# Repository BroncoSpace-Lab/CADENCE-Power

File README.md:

This repository contains the development of the Solar and Battery Management system Boards that will be used for the CADENCE mission.

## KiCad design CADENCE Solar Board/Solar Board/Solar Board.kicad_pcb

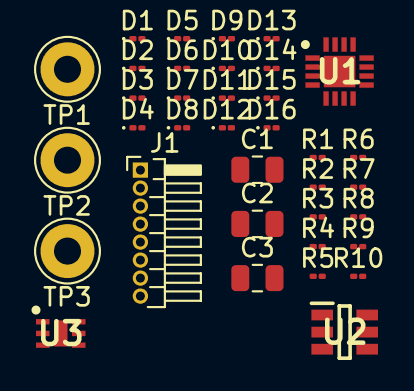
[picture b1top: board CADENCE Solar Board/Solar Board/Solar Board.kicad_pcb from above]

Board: 2 copper layers, 36 parts (0 on the bottom side), 32 nets, no tracks yet.

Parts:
C1, C3: 100nF; C_0805_2012Metric
C2: 10uF; C_0805_2012Metric
D1, D2, D3, D4, D5, D6, D7, D8, D9, D10, D11, D12, D13, D14, D15, D16: D; D_01005_0402Metric
J1: Conn_01x08; PinHeader_1x08_P1.00mm_Horizontal
R1, R2, R3, R5, R6, R7, R8, R10: 10k; R_01005_0402Metric
R4: 0.01; R_01005_0402Metric
R9: 1k; R_01005_0402Metric
TP1: Sensor Input; Pin_D1.3mm_L11.0mm_LooseFit
TP2: S1+; Pin_D1.3mm_L11.0mm_LooseFit
TP3: S1-; Pin_D1.3mm_L11.0mm_LooseFit
U1: INA230AIRGTT; QFN50P300X300X100-17N-D
U2: AD7414ARTZ-1REEL7; SOT95P280X145-6N
U3: OPT3001IDNPRQ1; SON65P200X200X65-7N-D

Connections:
+3.3V: C1.2, J1.1, R1.2, R4.1, R7.1, R8.2, R10.2, TP1.1 (1_1), U1.11 (BUS), U1.12 (IN-), U2.3 (VDD), U3.1 (VDD)
GND: C1.1, C2.2, C3.2, J1.4, U1.1 (A1), U1.2 (A0), U1.10 (GND), U2.2 (GND), U3.2 (ADDR), U3.3 (GND_1), U3.7 (GND_2)
HS_I2C1_LCL: J1.7, R3.2, R5.1, U3.4 (SCL)
HS_I2C1_LDA: J1.8, R2.1, R6.1, U3.6 (SDA)
unnamed: D1.2 (A), D2.2 (A)
unnamed: D1.1 (K), D4.2 (A)
unnamed: D2.1 (K), D3.2 (A)
unnamed: D3.1 (K), D6.2 (A)
unnamed: D4.1 (K), D8.2 (A)
unnamed: D5.2 (A), D6.1 (K)
unnamed: D7.2 (A), D8.1 (K)
unnamed: D5.1 (K), D10.2 (A)
unnamed: D9.2 (A), D10.1 (K)
unnamed: D11.2 (A), D12.1 (K)
unnamed: D11.1 (K), D16.2 (A)
unnamed: D7.1 (K), D12.2 (A)
unnamed: D13.2 (A), D14.1 (K)
unnamed: D13.1 (K), D15.1 (K)
unnamed: D9.1 (K), D14.2 (A)
unnamed: D15.2 (A), D16.1 (K)
unnamed: R1.1, U1.3 (ALERT)
unnamed: R4.2, U1.13 (IN+)
unnamed: R3.1, U1.5 (SCL)
unnamed: R2.2, U1.4 (SDA)
unnamed: R10.1, U1.9 (V_S+)
unnamed: C2.1, C3.1, R7.2, R9.2, U2.5 (ALERT)
unnamed: R9.1, U2.1 (AS)
unnamed: R5.2, U2.4 (SCL)
unnamed: R6.2, U2.6 (SDA)
unnamed: R8.1, U3.5 (INT)
Solar1+: J1.2, J1.3, TP2.1 (1_1)
Solar1-: J1.5, J1.6, TP3.1 (1_1)

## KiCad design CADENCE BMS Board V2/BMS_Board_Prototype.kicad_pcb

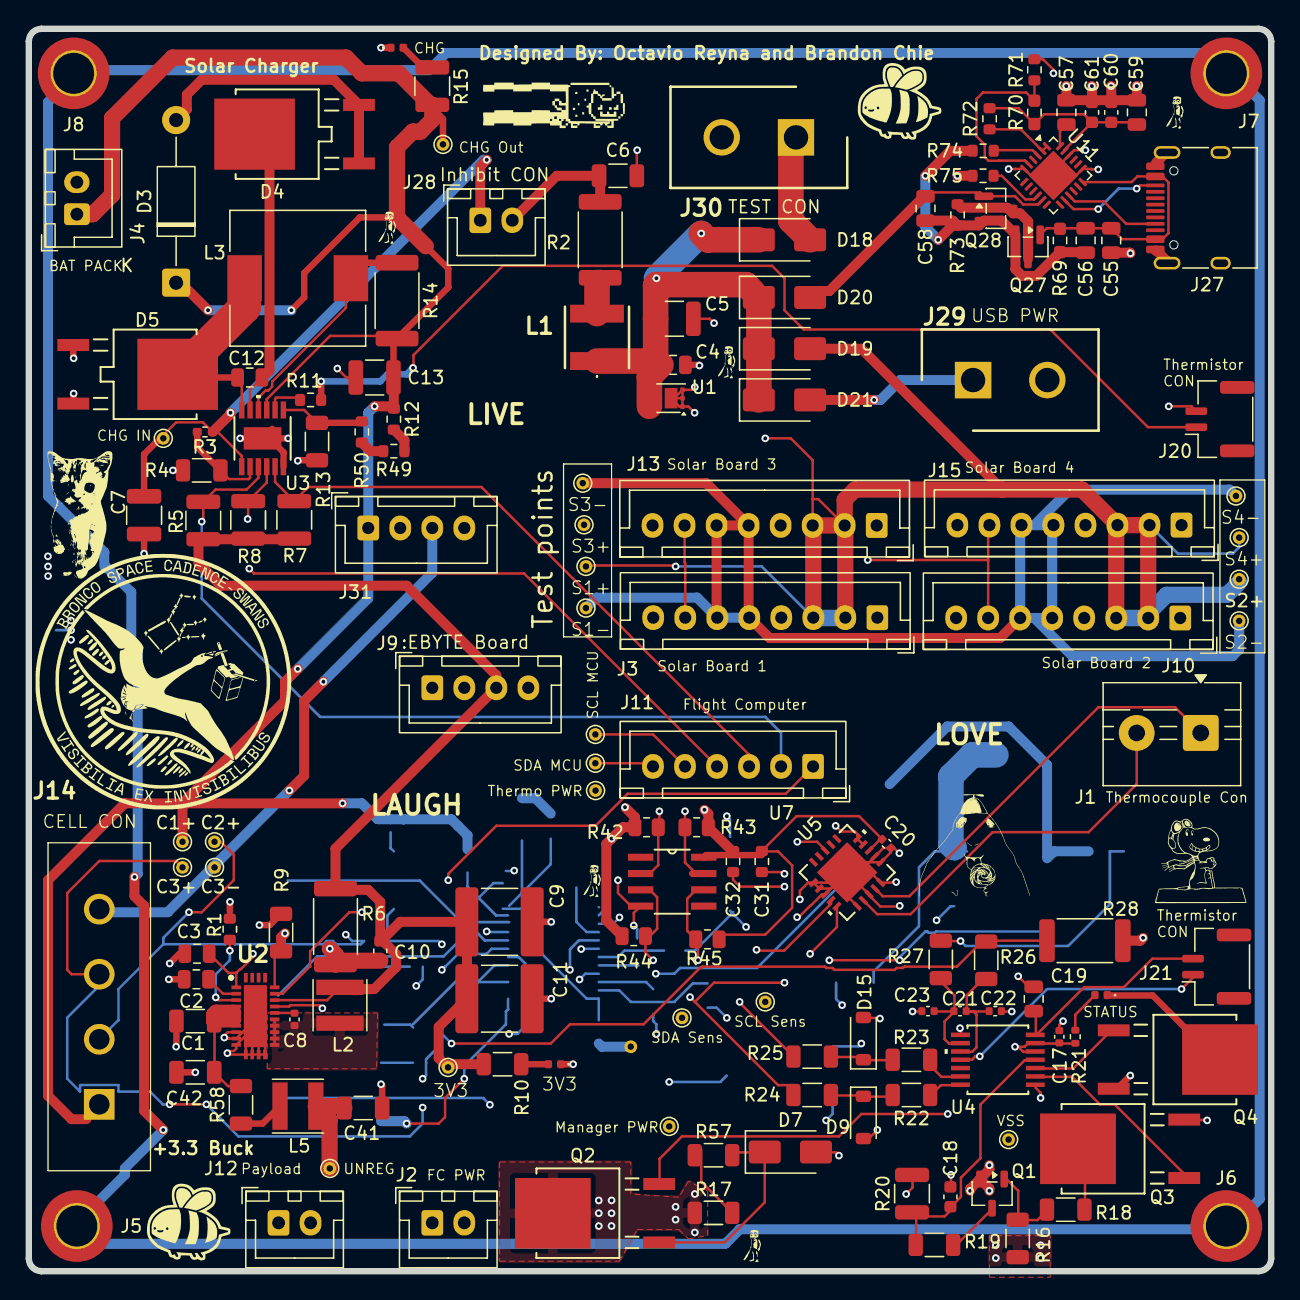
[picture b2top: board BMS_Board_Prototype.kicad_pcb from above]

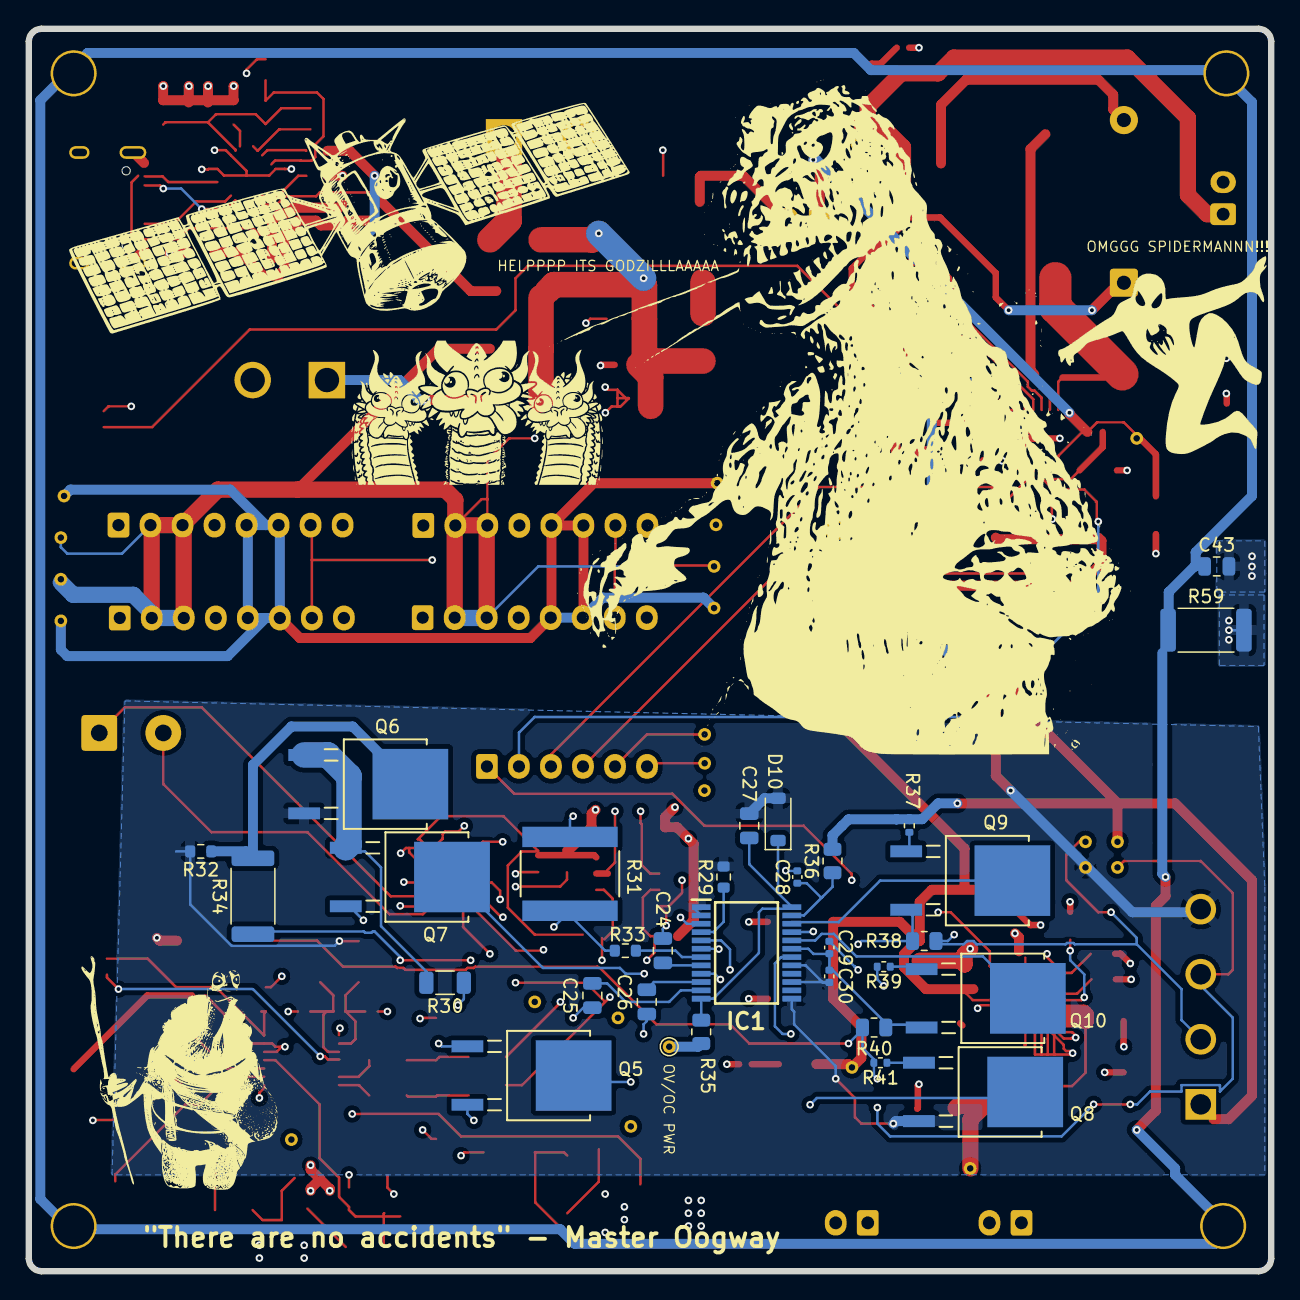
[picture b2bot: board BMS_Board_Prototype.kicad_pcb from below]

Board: 4 copper layers, 97.0 x 97.0 mm, 180 parts (31 on the bottom side), 98 nets.

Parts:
C1, C6, C41, C42: 4.7uF; C_1206_3216Metric
C1+: C1+; TestPoint_THTPad_D1.0mm_Drill0.5mm
C2, C4: 10nF; C_0805_2012Metric
C2+: C2+; TestPoint_THTPad_D1.0mm_Drill0.5mm
C3, C12, C19, C27, C56, C57, C58, C59: 1uF; C_0805_2012Metric
C3+: C3+; TestPoint_THTPad_D1.0mm_Drill0.5mm
C3-: C3-; TestPoint_THTPad_D1.0mm_Drill0.5mm
C5, C7, C13: 10uF; C_1210_3225Metric
C8, C17, C20, C21, C22, C23, C28, C29, C30: 100nF; C_0402_1005Metric
C9, C11: 47uF; C_2220_5750Metric
C10: 4.7pF; C_0603_1608Metric
C18: 3300pF; C_0603_1608Metric
C24, C55: 3.3uF; C_0805_2012Metric
C25: 2200pF; C_0805_2012Metric
C26: .47uF; C_0805_2012Metric
C31: 1uF; R_0603_1608Metric
C32: 100nF; R_0603_1608Metric
C43: 1nF; C_0805_2012Metric
C60, C61: 100nF; C_0603_1608Metric
D2: 3V3; LED_0402_1005Metric
D3: 1N4730APF-M (3V9); D_DO-41_SOD81_P12.70mm_Horizontal
D4, D5: STPS1045B-TR; DPAK_STM
D6: CHG; LED_0402_1005Metric
D7: 5V6; D_SMA
D8: LED; D_0402_1005Metric
D9, D15: 3.5V; D_SOD-123
D10: 15V; D_SOD-123
D18, D19, D20, D21: D_Schottky 40v; D_SMA
IC1: R5432V407BA; SOP65P760X140-24N
J1: Screw_Terminal_01x02; TerminalBlock_MaiXu_MX126-5.0-02P_1x02_P5.00mm
J2, J4, J12, J28: Conn_01x02; JST_XH_B2B-XH-A_1x02_P2.50mm_Vertical
J3, J10, J13, J15: Conn_01x08; JST_XH_B8B-XH-A_1x08_P2.50mm_Vertical
J5, J6, J7, J8: Conn_01x01_Socket; MountingHole_3.2mm_M3_DIN965_Pad_TopOnly
J9, J31: Conn_01x04; JST_XH_B4B-XH-A_1x04_P2.50mm_Vertical
J11: Conn_01x06; JST_XH_B6B-XH-A_1x06_P2.50mm_Vertical
J14: Conn_01x04; LC04T
J20, J21: Conn_01x02; JST_GH_SM02B-GHS-TB_1x02-1MP_P1.25mm_Horizontal
J27: USB_C_Receptacle_USB2.0_16P; USB_C_Receptacle_HRO_TYPE-C-31-M-12
J29, J30: Conn_01x02; SHDR2W120P580X500_2X1_790X1380X1460P
L1: 4.7u; FNR5040S4R7MT
L2: 1.8uH; L_Taiyo-Yuden_NR-40xx
L3: 22uH; L_10.4x10.4_H4.8
L5: 1uH; L_Taiyo-Yuden_NR-40xx
Q1: P-Channel FET; SOT-23-3
Q2, Q3, Q4: 60V Enhancement; SOT_N06-31-GE3_VIS
Q5, Q6, Q7: Q_NMOS_DSG; SOT_N06-31-GE3_VIS
Q8, Q9, Q10: N-MOS; SOT_N06-31-GE3_VIS
Q27, Q28: Q_PMOS_DGS; SOT-23
R1: 18.2k; R_0603_1608Metric
R2, R14: 0.1; R_2512_6332Metric
R3: 590k; R_0402_1005Metric_Pad0.72x0.64mm_HandSolder
R4, R16: 100k; R_1206_3216Metric
R5: 47k; R_1210_3225Metric
R6, R34, R59: 1M; R_2512_6332Metric
R7, R8: 10k; R_1210_3225Metric
R9: 412k; R_1206_3216Metric
R10: 4.7K; R_1206_3216Metric
R11: 910; R_0603_1608Metric
R12, R49: 470k; R_0603_1608Metric
R13: 340k; R_1206_3216Metric
R15: 10K; R_1210_3225Metric
R17, R57: 52.3k; R_1206_3216Metric
R18: 165k; R_1206_3216Metric
R19: 215K; R_1206_3216Metric
R20: 16.5k; R_1210_3225Metric
R21: 330; R_0402_1005Metric
R22, R23, R24, R25, R26, R27: 100; R_1206_3216Metric
R28: .037; R_2512_6332Metric
R29, R33, R75: 10K; R_0603_1608Metric
R30: 11.5K; R_1206_3216Metric
R31: .05; STA_CSSH2728_STP
R32: 2M; R_0603_1608Metric
R35, R36, R38, R40, R42, R43: 330; R_0805_2012Metric
R37, R39, R41: 100; R_0402_1005Metric
R44, R45: 4.7K; R_0805_2012Metric
R50: 1k; R_0603_1608Metric
R58: 0.1; R_1206_3216Metric
R69: 10K; R_0603_1608Metric_Pad0.98x0.95mm_HandSolder
R70: 5.1K; R_0603_1608Metric_Pad0.98x0.95mm_HandSolder
R71: 2.4K; R_0603_1608Metric
R72: 0; R_0603_1608Metric
R73, R74: 49.9K; R_0603_1608Metric
TP1: UNREG; TestPoint_THTPad_D1.0mm_Drill0.5mm
TP2: Charger-IN; TestPoint_THTPad_D1.0mm_Drill0.5mm
TP3: 3V3; TestPoint_THTPad_D1.0mm_Drill0.5mm
TP4: Charger-Out; TestPoint_THTPad_D1.0mm_Drill0.5mm
TP5: Manager-PWR; TestPoint_THTPad_D1.0mm_Drill0.5mm
TP6: VSS; TestPoint_THTPad_D1.0mm_Drill0.5mm
TP7: Thermo-PWR; TestPoint_THTPad_D1.0mm_Drill0.5mm
TP8: OV/OC PWR; TestPoint_THTPad_D1.0mm_Drill0.5mm
TP9: S1-; TestPoint_THTPad_D1.0mm_Drill0.5mm
TP10: S1+; TestPoint_THTPad_D1.0mm_Drill0.5mm
TP11: S2+; TestPoint_THTPad_D1.0mm_Drill0.5mm
TP12: S2-; TestPoint_THTPad_D1.0mm_Drill0.5mm
TP13: S3+; TestPoint_THTPad_D1.0mm_Drill0.5mm
TP14: S3-; TestPoint_THTPad_D1.0mm_Drill0.5mm
TP15: S4+; TestPoint_THTPad_D1.0mm_Drill0.5mm
TP16: S4-; TestPoint_THTPad_D1.0mm_Drill0.5mm
TP17: SDA-MCU; TestPoint_THTPad_D1.0mm_Drill0.5mm
TP18: SCL-MCU; TestPoint_THTPad_D1.0mm_Drill0.5mm
TP19: SDA-Sensor; TestPoint_THTPad_D1.0mm_Drill0.5mm
TP20: SCL-Sensor; TestPoint_THTPad_D1.0mm_Drill0.5mm
U1: TVS2200DRV; WSON-6-1EP_2x2mm_P0.65mm_EP1x1.6mm
U2: LT8612; QFN50P300X600X80-29N-D
U3: LT3652IMSE#PBF; MSOP-12_MSE_LIT
U4: BQ34Z100-R2; PW14_TEX
U5: MCP9600-E_MX; MQFN20_NU_MCH
U7: P82B715DR; D8
U11: CYPD3177-24LQ; QFN-24-1EP_4x4mm_P0.5mm_EP2.75x2.75mm

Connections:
3V3 Power Good: J11.1, U2.23 (PG)
+3.3V: C9.2, C10.2, C11.2, C20.2, C31.1, C32.1, J3.1, J9.3, J10.1, J13.1, J15.1, L2.2, R5.1, R6.2, R7.1, R8.1, R10.1, R42.1, R43.1, R44.1, R45.1, R75.1, TP3.1 (1_1), TP7.1 (1_1), U2.22 (BIAS), U5.8 (VDD), U7.8 (Vcc)
/Power/3v3 Feedback: C10.1, R6.1, R9.1, U2.24 (FB)
/Power/3v3 SW: C8.1, L2.1, U2.15 (SW), U2.16 (SW), U2.17 (SW), U2.18 (SW), U2.19 (SW)
/Sensors/REGIN: C17.1, Q2.2 (S), R21.1, U4.5 (CE), U4.6 (REGIN)
/Sensors/Serial Clock: R23.1, U4.13 (P4/SCL)
/Sensors/Serial Data: R22.1, U4.14 (P3/SDA)
/Sensors/Voltage Divider: C18.2, R19.2, R20.1, U4.4 (BAT)
/Sensors/Voltage Divider Enable: Q3.3 (D), R18.2
CB1: IC1.22 (CB1), Q9.3 (G)
CB2: IC1.20 (CB2), Q10.3 (G)
CB3: IC1.18 (CB3), Q8.3 (G)
CC1: J27.A5 (CC1), U11.15 (CC1)
CC2: J27.B5 (CC2), U11.14 (CC2)
CHG': J11.4, R8.2, U3.4 (~CHRG)
Cell 1+: C1+.1 (1_1), C13.1, D3.1 (K), J4.1, J14.1, J31.1, R12.1, R14.2, R15.1, R36.2, R37.2, TP4.1 (1_1), U3.9 (BAT)
Cell 2+: C2+.1 (1_1), J14.2, R38.2, R39.2
Cell 3+: C3+.1 (1_1), J14.3, R26.2, R28.1, R40.2, R41.2
Cell 3-: C3-.1 (1_1), C27.2, C30.2, D10.2 (A), IC1.1 (CTLC), IC1.2 (CTLD), IC1.13 (SEL2), IC1.15 (VC5), IC1.17 (VC4), J14.4, J31.3, Q6.2 (S), Q8.2 (S), R27.2, R28.2, R29.2, R32.2
DRAIN: IC1.5 (DRAIN), Q5.3 (G)
FAULT': J11.3, R7.2, U3.5 (~FAULT)
HS_I2C1_LCL: J3.7, J10.7, J11.5, J13.7, J15.7, R43.2, TP18.1 (1_1), U7.7 (Ly)
HS_I2C1_LDA: J3.8, J10.8, J11.6, J13.8, J15.8, R42.2, TP17.1 (1_1), U7.2 (Lx)
HS_I2C1_SCL: R25.2, R45.2, TP20.1 (1_1), U5.19 (SCL), U7.6 (Sy)
HS_I2C1_SDA: R24.2, R44.2, TP19.1 (1_1), U5.20 (SDA), U7.3 (Sx)
NTC: J20.1, R11.2
unnamed: C43.1, J5.1 (1_1), J6.1 (1_1), J7.1 (1_1), J8.1 (1_1), R59.1
unnamed: D2.2 (A), R10.2
unnamed: D3.2 (A), D4.1 (A)
unnamed: C12.2, D4.2 (K), U3.11 (BOOST)
unnamed: C12.1, D5.2 (K), L3.1, U3.12 (SW)
unnamed: D6.2 (A), R15.2
unnamed: D7.1 (K), Q2.1 (G), R57.2
unnamed: D8.2 (A), R21.2
unnamed: D8.1 (K), Q4.3 (D)
unnamed: D9.1 (K), R22.2, R24.1
unnamed: D15.1 (K), R23.2, R25.1
unnamed: C4.1, C5.1, D18.1 (K), D19.1 (K), D20.1 (K), D21.1 (K), L1.1, U1.4 (IN), U1.5 (IN), U1.6 (IN)
unnamed: IC1.3 (COUT), R34.1
unnamed: C26.2, IC1.10 (CT1)
unnamed: C25.1, IC1.11 (CT2)
unnamed: C24.2, IC1.8 (CTLT)
unnamed: IC1.6 (DOUT), Q7.3 (G)
unnamed: IC1.7 (SENS), R33.2
unnamed: C28.1, IC1.23 (VC1), R36.1
unnamed: C28.2, C29.1, IC1.21 (VC2), Q9.2 (S), R38.1
unnamed: C29.2, C30.1, IC1.19 (VC3), Q10.2 (S), R40.1
unnamed: J1.1, U5.4 (VIN-)
unnamed: J1.2, U5.2 (VIN+)
unnamed: J21.1, U4.11 (P6/TS)
unnamed: L1.2, R2.1
unnamed: L5.2, R58.1
unnamed: Q1.3 (D), R19.1
unnamed: Q1.1 (G), R16.2, R18.1
unnamed: Q3.1 (G), U4.2 (VEN)
unnamed: Q4.1 (G), U4.3 (P1)
unnamed: Q5.1 (D), R30.1
unnamed: Q6.1 (D), Q7.1 (D), R30.2
unnamed: Q6.3 (G), R32.1, R34.2
unnamed: Q7.2 (S), R31.2, R33.1
unnamed: Q8.1 (D), R41.1
unnamed: Q9.1 (D), R37.1
unnamed: Q10.1 (D), R39.1
unnamed: C56.2, C58.2, Q27.2 (G), Q28.2 (G), R69.2, R73.2, R74.1
unnamed: Q27.3 (S), Q28.3 (S), R73.1
unnamed: R12.2, R49.1
unnamed: R17.2, R57.1
unnamed: R49.2, R50.1
unnamed: C8.2, U2.20 (BST)
unnamed: C1.1, C42.1, R58.2, U2.4 (EN/UV), U2.5 (VIN), U2.6 (VIN), U2.7 (VIN)
unnamed: C3.2, U2.1 (SYNC), U2.21 (INTVCC)
unnamed: R1.1, U2.3 (RT)
unnamed: C2.2, U2.2 (TR/SS)
unnamed: R11.1, U3.8 (NTC)
unnamed: L3.2, R14.1, U3.10 (SENSE)
unnamed: R13.1, R50.2, U3.7 (VFB)
unnamed: R3.2, R4.1, U3.2 (VIN_REG)
unnamed: C21.1, C22.2, R26.1, U4.10 (SRN)
unnamed: C21.2, C23.2, R27.1, U4.9 (SRP)
unnamed: R75.2, U11.10 (FLIP)
unnamed: R70.2, R71.1, U11.5 (ISNK_COARSE)
unnamed: R72.2, U11.1 (VBUS_MIN), U11.2 (VBUS_MAX)
unnamed: C57.2, U11.24 (VCCD)
REG25: C19.2, J21.2, U4.7 (REG25)
SHDN': J11.2, R5.2, U3.3 (~SHDN)
Solar1-: C1.2, C2.1, C3.1, C4.2, C5.2, C6.2, C7.2, C9.1, C11.1, C13.2, C17.2, C18.1, C19.1, C20.1, C22.1, C23.1, C24.1, C25.2, C26.1, C31.2, C32.2, C41.2, C42.2, C43.2, C55.2, C57.1, C59.2, C60.2, C61.2, D2.1 (K), D5.1 (A), D6.1 (K), D7.2 (A), D9.2 (A), D15.2 (A), IC1.9 (VSS), J2.2, J3.4, J3.5, J3.6, J4.2, J9.2, J9.4, J10.4, J10.5, J10.6, J12.2, J13.4, J13.5, J13.6, J15.4, J15.5, J15.6, J20.2, J27.A1 (GND), J27.A12 (GND), J27.B1 (GND), J27.B12 (GND), J27.SH (SHIELD), J29.2, J30.2, J31.4, Q3.2 (S), Q4.2 (S), Q5.2 (S), R1.2, R4.2, R9.2, R13.2, R20.2, R31.1, R59.2, R71.2, TP6.1 (1_1), TP9.1 (1_1), TP12.1 (1_1), TP14.1 (1_1), TP16.1 (1_1), U1.1 (GND), U1.2 (GND), U1.3 (GND), U1.7 (GND), U2.8 (PGND), U2.9 (PGND), U2.10 (PGND), U2.11 (GND), U2.12 (GND), U2.13 (GND), U2.14 (GND), U2.29 (GND), U3.6 (TIMER), U3.13 (GND), U4.1 (P2), U4.8 (VSS), U5.1 (GND), U5.3 (GND), U5.5 (GND), U5.6 (GND), U5.7 (GND), U5.9 (GND), U5.10 (GND), U5.13 (GND), U5.16 (ADDR), U5.17 (GND), U5.18 (GND), U5.21 (EXP), U7.4 (GND), U11.6 (ISNK_FINE), U11.19 (GND), U11.22 (GND), U11.25 (GND)
Solar Power: D19.2 (A), J3.2, J3.3, J10.2, J10.3, J13.2, J13.3, J15.2, J15.3, TP10.1 (1_1), TP11.1 (1_1), TP13.1 (1_1), TP15.1 (1_1)
TEST_PWR: D18.2 (A), J30.1
UNREG: C41.1, J2.1, J9.1, J12.1, J31.2, L5.1, Q1.2 (S), Q2.3 (D), R16.1, R17.1, R35.1, TP1.1 (1_1), TP5.1 (1_1), TP8.1 (1_1)
USB PWR: D21.2 (A), J29.1
VBUS: C55.1, C56.1, J27.A4 (VBUS), J27.A9 (VBUS), J27.B4 (VBUS), J27.B9 (VBUS), Q27.1 (D), R69.1, U11.18 (VBUS_IN)
VBUS_EN: R74.2, U11.3 (VBUS_FET_EN)
VDC_OUT: C58.1, D20.2 (A), Q28.1 (D), U11.11 (VDC_OUT)
VDD: C27.1, D10.1 (K), IC1.12 (SEL1), IC1.24 (VDD), R35.2
VDDD: C59.1, C60.1, C61.1, R70.1, R72.1, U11.23 (VDDD)
VMP: IC1.4 (VMP), R29.1
V_mppt_i: C6.1, J28.2, R2.2
V_mppt_o: C7.1, J28.1, R3.1, TP2.1 (1_1), U3.1 (VIN)

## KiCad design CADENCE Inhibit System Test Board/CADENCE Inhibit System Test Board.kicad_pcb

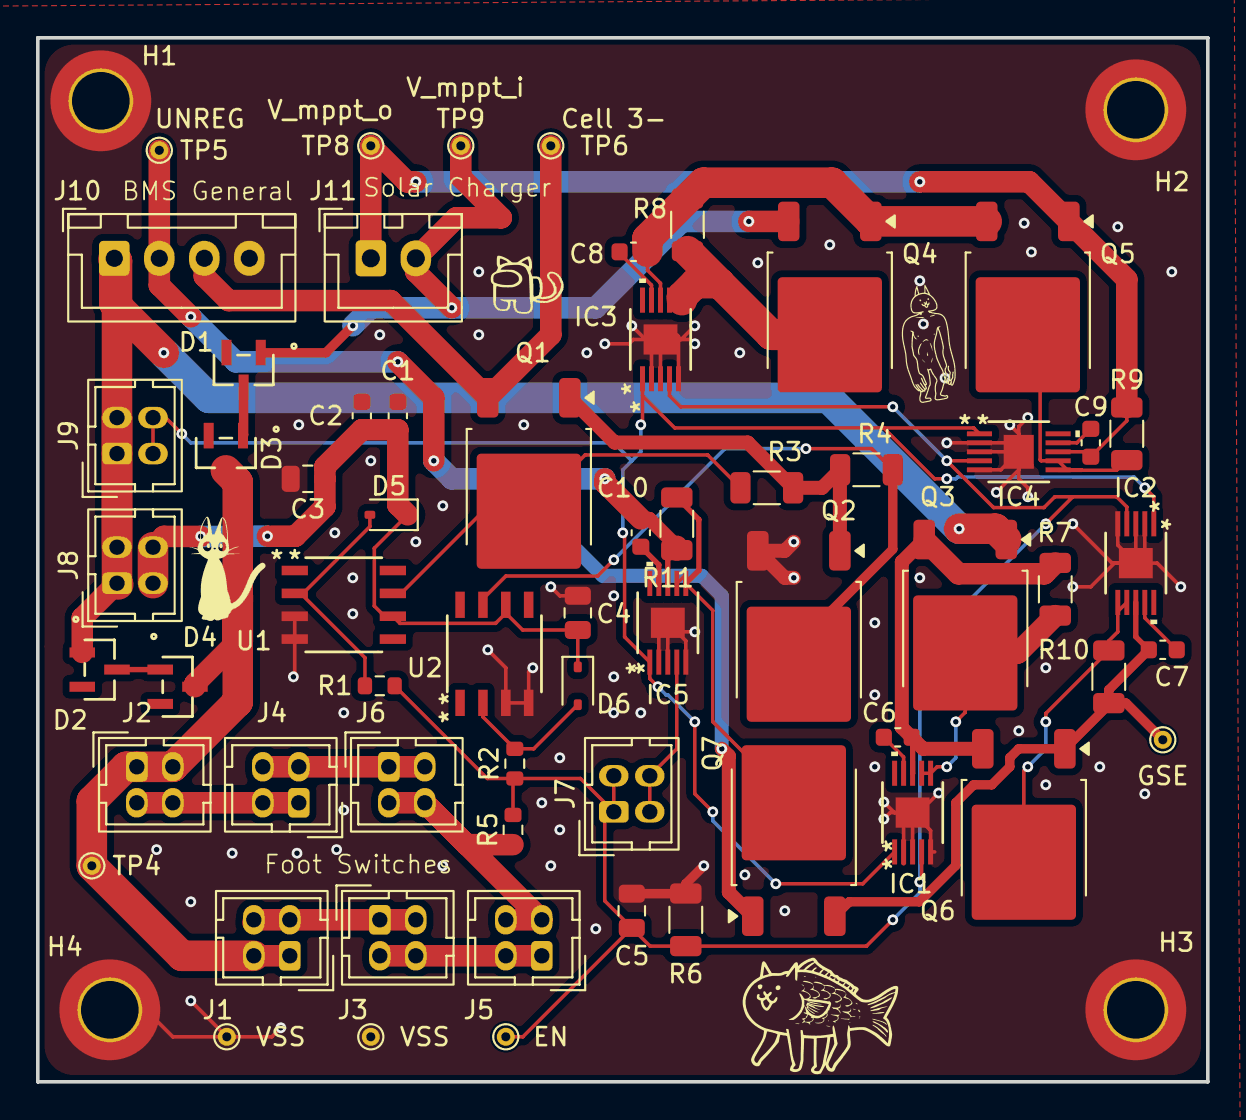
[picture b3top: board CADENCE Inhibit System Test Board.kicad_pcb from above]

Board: 2 copper layers, 65.0 x 58.0 mm, 65 parts (0 on the bottom side), 36 nets.

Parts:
C1, C2, C6, C7, C8, C9, C10: 100nF; C_0603_1608Metric
C3, C4: 4.7uF; C_0805_2012Metric
C5: 10nF; C_0805_2012Metric
D1, D2, D3, D4: MMBD914LT1G; SOT-23_ONS
D5, D6: 1N5711WS-7-F; D_SOD-323
GSE: GSE; TestPoint_THTPad_D1.0mm_Drill0.5mm
H1, H2, H3, H4: MountingHole_Pad; MountingHole_3.2mm_M3_DIN965_Pad_TopOnly
IC1, IC2, IC3, IC4, IC5: LTC7004IMSE#WTRPBF; MSE_05-08-1664_ADI
J1, J2, J3, J4, J5, J6, J7, J8, J9: INHIBIT_P2; Hirose_DF11-4DP-2DSA_2x02_P2.00mm_Vertical
J10: Conn_01x04; JST_XH_B4B-XH-A_1x04_P2.50mm_Vertical
J11: Conn_01x02; JST_XH_B2B-XH-A_1x02_P2.50mm_Vertical
Q1, Q2, Q3, Q4, Q5, Q6, Q7: SUD23N06-31-GE3; TO-252-2
R1, R2: 47k; R_0603_1608Metric
R3, R4, R7, R8, R9, R10, R11: 100K; R_1206_3216Metric
R5: 39k; R_0603_1608Metric
R6: 100k; R_1206_3216Metric
TP1, TP7: VSS; TestPoint_THTPad_D1.0mm_Drill0.5mm
TP2: EN; TestPoint_THTPad_D1.0mm_Drill0.5mm
TP4: Voltage Level; TestPoint_THTPad_D1.0mm_Drill0.5mm
TP5: UNREG; TestPoint_THTPad_D1.0mm_Drill0.5mm
TP6: Cell 3-; TestPoint_THTPad_D1.0mm_Drill0.5mm
TP8: V_mppt_o; TestPoint_THTPad_D1.0mm_Drill0.5mm
TP9: V_mppt_i; TestPoint_THTPad_D1.0mm_Drill0.5mm
U1, U2: MIC4427YM-TR; SOIC-8_M_MCH

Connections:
Cell 1+: D2.1 (K_1), J8.1, J8.3, J9.1, J9.3, J10.1, Q3.1 (S)
Cell 3-: J10.3, Q1.3 (D), TP6.1 (1_1)
EN: C5.2, IC1.4 (INP), IC2.4 (INP), IC3.4 (INP), IC4.4 (INP), J7.1, J7.3, R1.1, R2.1, R5.2, R6.1, TP2.1 (1_1)
HIGH_SIDE_PWR: IC1.1 (VCC), IC2.1 (VCC), IC3.1 (VCC), IC4.1 (VCC), IC5.1 (VCC), J9.2, J9.4
LOW_SIDE_PWR: C1.1, C2.1, C3.1, C4.1, D5.1 (K), D6.1 (K), J8.2, J8.4, U1.6 (V_{S}), U2.6 (V_{S})
unnamed: D1.3, D3.1 (K_1)
unnamed: D2.3 (A_2), D4.1 (K_1)
unnamed: D3.3, D4.3 (A_2), J1.1, J1.3, J2.1, J2.3, TP4.1 (1_1)
unnamed: D5.2 (A), R1.2, U1.2 (INA)
unnamed: D6.2 (A), R2.2, U2.2 (INA)
unnamed: C6.2, IC1.9 (BST)
unnamed: IC1.6 (TGDN), IC1.7 (TGUP), Q3.2 (G), R7.2
unnamed: C6.1, IC1.8 (TS), Q3.3 (D), Q6.3 (D), R7.1
unnamed: C7.2, IC2.9 (BST)
unnamed: IC2.6 (TGDN), IC2.7 (TGUP), Q6.2 (G), R10.2
unnamed: C7.1, GSE.1 (1_1), IC2.8 (TS), Q6.1 (S), Q7.3 (D), R10.1
unnamed: C8.2, IC3.9 (BST)
unnamed: IC3.6 (TGDN), IC3.7 (TGUP), Q4.2 (G), R8.2
unnamed: C8.1, IC3.8 (TS), Q4.1 (S), Q5.3 (D), R8.1
unnamed: C9.2, IC4.9 (BST)
unnamed: IC4.6 (TGDN), IC4.7 (TGUP), Q5.2 (G), R9.2
unnamed: C10.2, IC5.9 (BST)
unnamed: IC5.4 (INP), J7.2, J7.4
unnamed: IC5.6 (TGDN), IC5.7 (TGUP), Q7.2 (G), R11.2
unnamed: J1.2, J1.4, J3.1, J3.3
unnamed: J2.2, J2.4, J4.1, J4.3
unnamed: J3.2, J3.4, J5.1, J5.3
unnamed: J4.2, J4.4, J6.1, J6.3
unnamed: J5.2, J5.4, J6.2, J6.4, R5.1
unnamed: Q1.2 (G), R3.2, U1.7 (OUTA)
unnamed: Q1.1 (S), Q2.1 (S), R3.1, R4.2
unnamed: Q2.2 (G), R4.1, U2.7 (OUTA)
UNREG: C10.1, IC5.8 (TS), J10.2, Q7.1 (S), R11.1, TP5.1 (1_1)
VSS: C1.2, C2.2, C3.2, C4.2, C5.1, H1.1 (1_1), H2.1 (1_1), H3.1 (1_1), H4.1 (1_1), IC1.2 (VCCUV), IC1.3 (GND_1), IC1.5 (OVLO), IC1.11 (GND_2), IC2.2 (VCCUV), IC2.3 (GND_1), IC2.5 (OVLO), IC2.11 (GND_2), IC3.2 (VCCUV), IC3.3 (GND_1), IC3.5 (OVLO), IC3.11 (GND_2), IC4.2 (VCCUV), IC4.3 (GND_1), IC4.5 (OVLO), IC4.11 (GND_2), IC5.2 (VCCUV), IC5.3 (GND_1), IC5.5 (OVLO), IC5.11 (GND_2), J10.4, Q2.3 (D), R6.2, TP1.1 (1_1), TP7.1 (1_1), U1.3 (GND), U1.4 (INB), U2.3 (GND), U2.4 (INB)
V_mppt_i: D1.1 (K_1), J11.2, Q4.3 (D), TP9.1 (1_1)
V_mppt_o: C9.1, IC4.8 (TS), J11.1, Q5.1 (S), R9.1, TP8.1 (1_1)

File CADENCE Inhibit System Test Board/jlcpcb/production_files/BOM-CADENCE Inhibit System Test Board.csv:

Comment,Designator,Footprint,LCSC,Quantity
100K,"R10,R11,R3,R4,R7,R8,R9",R_1206_3216Metric,C17900,7
100k,R6,R_1206_3216Metric,C17900,1
100nF,"C1,C10,C2,C6,C7,C8,C9",C_0603_1608Metric,C1591,7
10nF,C5,C_0805_2012Metric,C1710,1
1N5711WS-7-F,"D5,D6",D_SOD-323,C151442,2
39k,R5,R_0603_1608Metric,C23153,1
4.7uF,"C3,C4",C_0805_2012Metric,C98192,2
47k,"R1,R2",R_0603_1608Metric,C25600,2
Conn_01x04,J10,JST_XH_B4B-XH-A_1x04_P2.50mm_Vertical,C594232,1
INHIBIT_P2,"J1,J2,J3,J4,J5,J6,J7,J8,J9",Hirose_DF11-4DP-2DSA_2x02_P2.00mm_Vertical,C506665,9
MIC4427YM-TR,"U1,U2",SOIC-8_M_MCH,C461590,2
MMBD914LT1G,"D1,D2,D3,D4",SOT-23_ONS,C46523,4

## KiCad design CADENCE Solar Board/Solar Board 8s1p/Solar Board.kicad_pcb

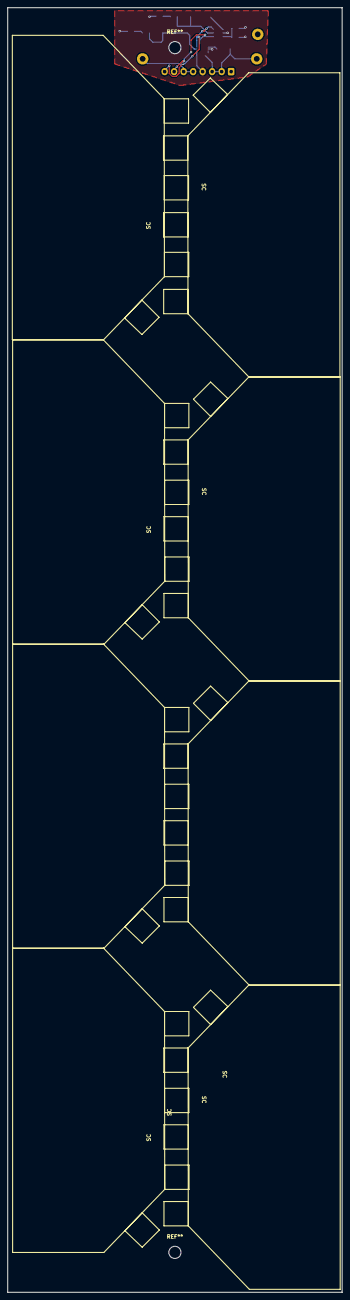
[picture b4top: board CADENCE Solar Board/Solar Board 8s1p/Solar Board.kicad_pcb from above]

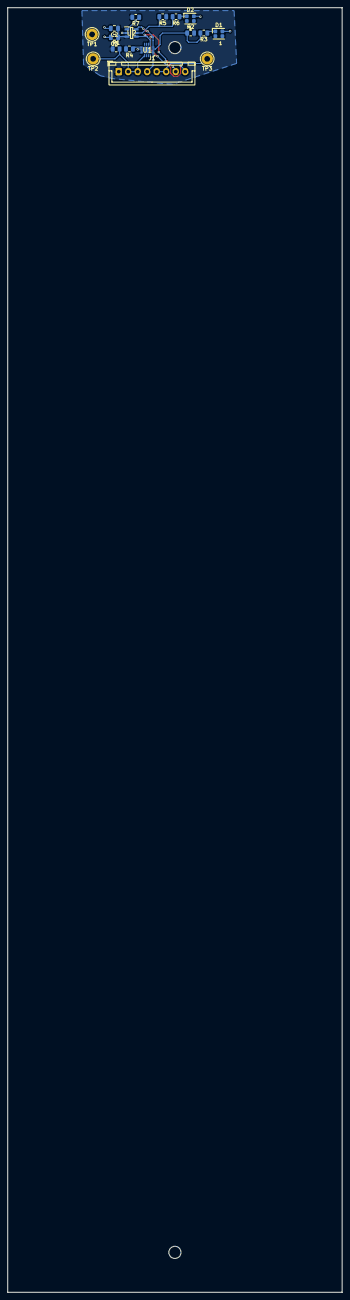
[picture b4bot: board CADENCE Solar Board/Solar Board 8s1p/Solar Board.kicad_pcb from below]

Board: 2 copper layers, 88.0 x 338.0 mm, 25 parts (17 on the bottom side), 12 nets.

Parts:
C2: 10uF; C_0805_2012Metric
C3: 100nF; C_0805_2012Metric
D1, D2: LED; LED_RGB_Lumex_SML-LXT0805SIUGUBW
J1: Conn_01x08; JST_XH_B8B-XH-A_1x08_P2.50mm_Vertical
R1: 0.01; R_0805_2012Metric
R2, R4, R5: 10k; R_0805_2012Metric
R3, R6: 500; R_0805_2012Metric
R7: 1k; R_0805_2012Metric
SC: CAVU Solar Cell
SC#2, SC#3, SC#4, SC#5, SC#6, SC#7, SC#8: CAVU Solar Cell
TP1: Sensor Input; Pin_D1.3mm_L11.0mm_LooseFit
TP2: S1+; Pin_D1.3mm_L11.0mm_LooseFit
TP3: S1-; Pin_D1.3mm_L11.0mm_LooseFit
U1: INA230AIRGTT; QFN50P300X300X100-17N-D
U2: AD7414ARTZ-1REEL7; SOT95P280X145-6N

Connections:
+3.3V: C2.1, C3.1, J1.1, R1.1, R2.2, R4.2, R5.1, R7.2, TP1.1 (1_1), U1.11 (BUS), U1.12 (IN-), U2.3 (VDD)
GND: C2.2, C3.2, D1.1 (K), D2.1 (K), J1.4, U1.1 (A1), U1.2 (A0), U1.10 (GND), U2.2 (GND)
HS_I2C1_LCL: J1.7, U1.5 (SCL), U2.4 (SCL)
HS_I2C1_LDA: J1.8, U1.4 (SDA), U2.6 (SDA)
unnamed: D1.2 (A), R3.1
unnamed: D2.2 (A), R6.1
unnamed: R2.1, R3.2, U1.3 (ALERT)
unnamed: R4.1, U1.9 (V_S+)
unnamed: R5.2, R6.2, U2.5 (ALERT)
unnamed: R7.1, U2.1 (AS)
Solar1+: J1.2, J1.3, R1.2, TP2.1 (1_1), U1.13 (IN+)
Solar1-: J1.5, J1.6, TP3.1 (1_1)
